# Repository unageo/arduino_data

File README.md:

# External Tachometer for Racing Games

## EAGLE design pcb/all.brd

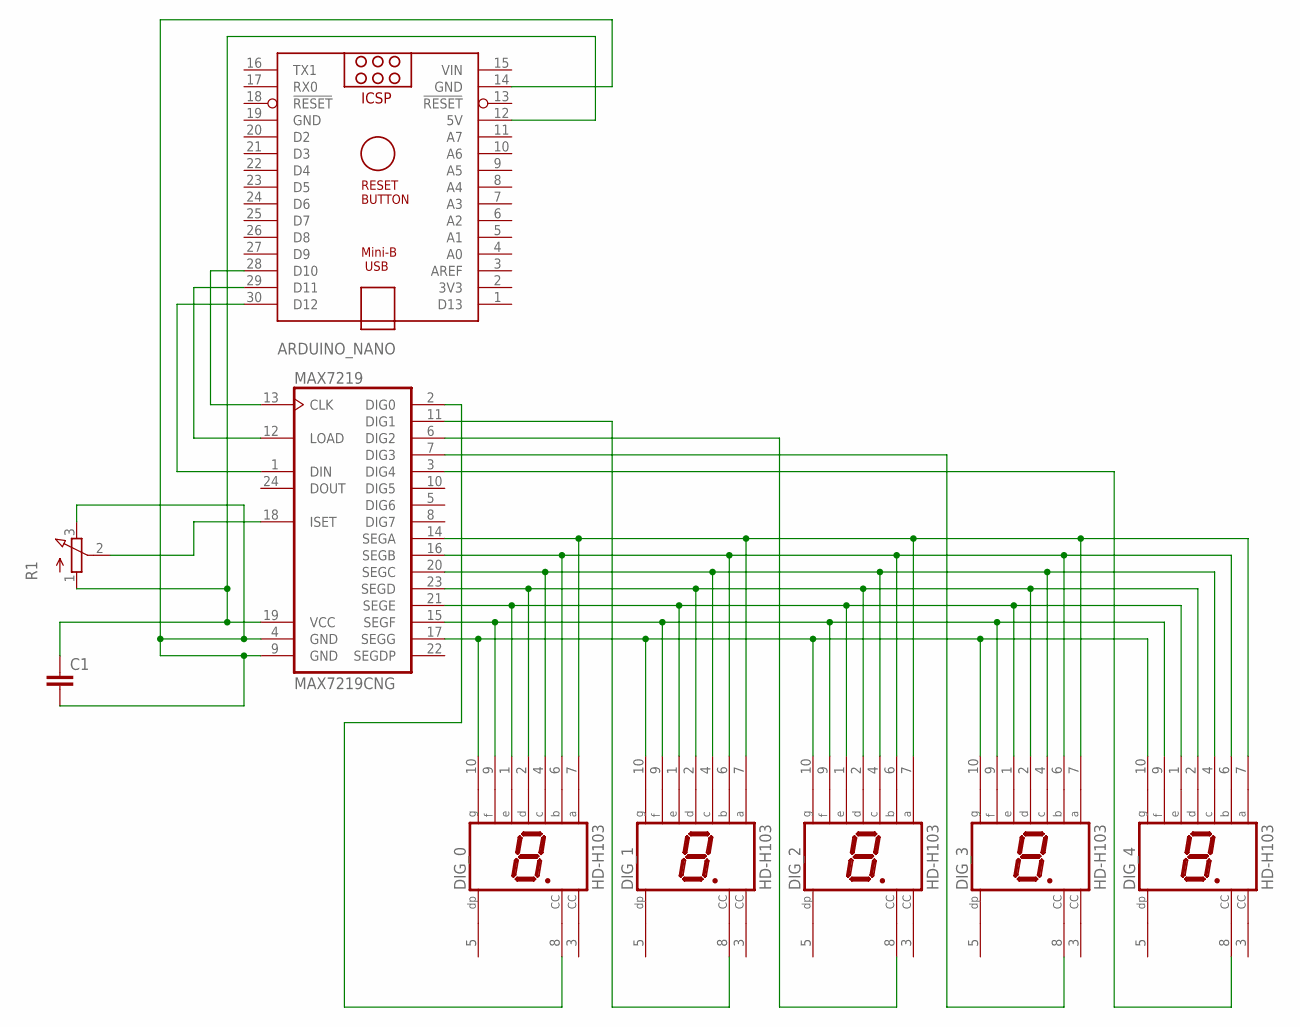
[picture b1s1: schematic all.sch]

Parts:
ARDUINO_NANO: ARDUINO_NANO
C1: C2,5-3; C2.5-3
DIG_0, DIG_1, DIG_2, DIG_3, DIG_4: HD-H103; HDSP-M
MAX7219: MAX7219CNG; DIL24-3
R1: 3RP/1610N

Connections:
GND: ARDUINO_NANO.19 (GND)
unnamed: DIG_1.8 (CC), MAX7219.11 (DIG1)
unnamed: DIG_0.8 (CC), MAX7219.2 (DIG0)
unnamed: DIG_2.8 (CC), MAX7219.6 (DIG2)
unnamed: DIG_3.8 (CC), MAX7219.7 (DIG3)
unnamed: DIG_4.8 (CC), MAX7219.3 (DIG4)
unnamed: DIG_0.7 (A), DIG_1.7 (A), DIG_2.7 (A), DIG_3.7 (A), DIG_4.7 (A), MAX7219.14 (SEGA)
unnamed: DIG_0.6 (B), DIG_1.6 (B), DIG_2.6 (B), DIG_3.6 (B), DIG_4.6 (B), MAX7219.16 (SEGB)
unnamed: DIG_0.4 (C), DIG_1.4 (C), DIG_2.4 (C), DIG_3.4 (C), DIG_4.4 (C), MAX7219.20 (SEGC)
unnamed: DIG_0.2 (D), DIG_1.2 (D), DIG_2.2 (D), DIG_3.2 (D), DIG_4.2 (D), MAX7219.23 (SEGD)
unnamed: DIG_0.1 (E), DIG_1.1 (E), DIG_2.1 (E), DIG_3.1 (E), DIG_4.1 (E), MAX7219.21 (SEGE)
unnamed: DIG_0.9 (F), DIG_1.9 (F), DIG_2.9 (F), DIG_3.9 (F), DIG_4.9 (F), MAX7219.15 (SEGF)
unnamed: DIG_0.10 (G), DIG_1.10 (G), DIG_2.10 (G), DIG_3.10 (G), DIG_4.10 (G), MAX7219.17 (SEGG)
unnamed: ARDUINO_NANO.28 (D10), MAX7219.13 (CLK)
unnamed: ARDUINO_NANO.29 (D11), MAX7219.12 (LOAD)
unnamed: ARDUINO_NANO.30 (D12), MAX7219.1 (DIN)
unnamed: ARDUINO_NANO.12 (5V), C1.1, MAX7219.19 (VCC), R1.1 (A)
unnamed: MAX7219.18 (ISET), R1.2 (S)
unnamed: ARDUINO_NANO.14 (GND), C1.2, MAX7219.4 (GND), MAX7219.9 (GND), R1.3 (E)
VIN: ARDUINO_NANO.15 (VIN)

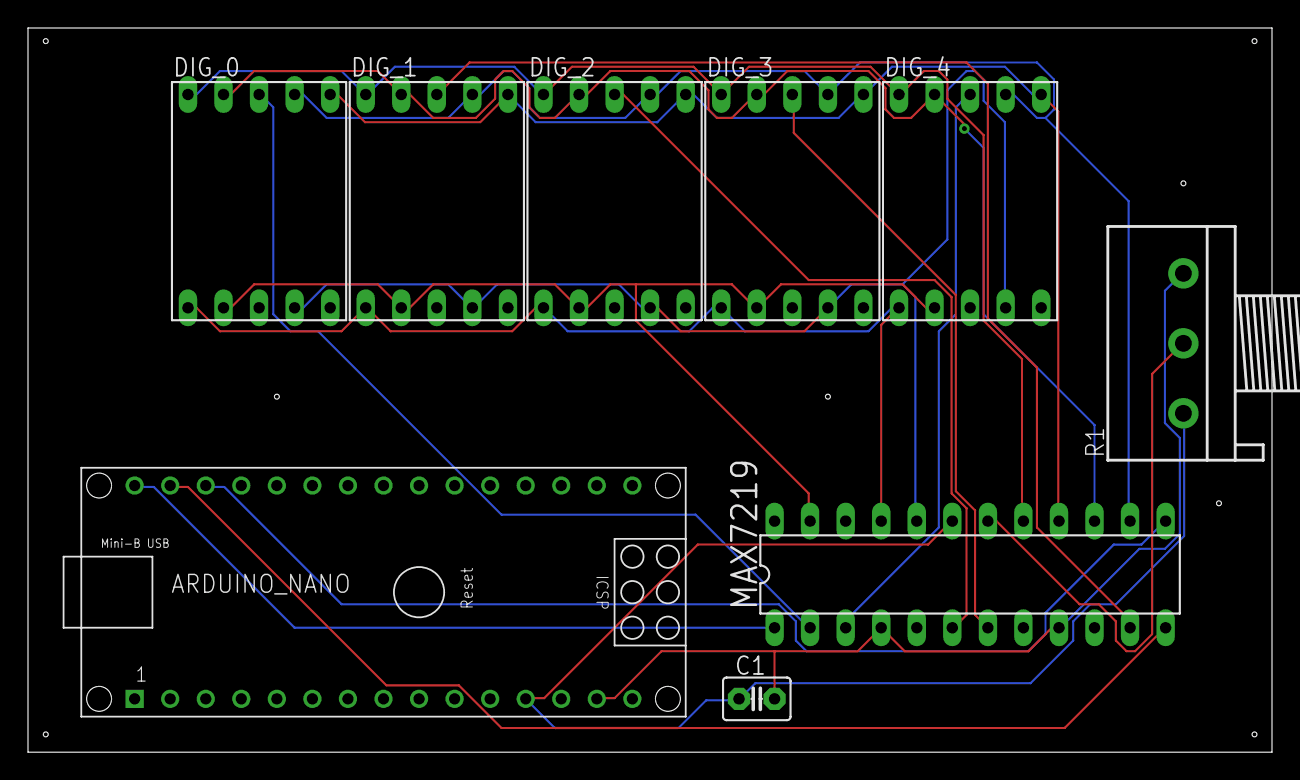
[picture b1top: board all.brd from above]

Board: 2 copper layers, 88.9 x 51.7 mm, 9 parts (0 on the bottom side), 18 nets.

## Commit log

2021-06-12 create folder for my java project
2021-06-12 move to jvm
2021-06-12 eagle stuff
2021-06-12 Add arduino code
